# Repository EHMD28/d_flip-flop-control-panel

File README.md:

# D-Type Flip-Flop Control Panel

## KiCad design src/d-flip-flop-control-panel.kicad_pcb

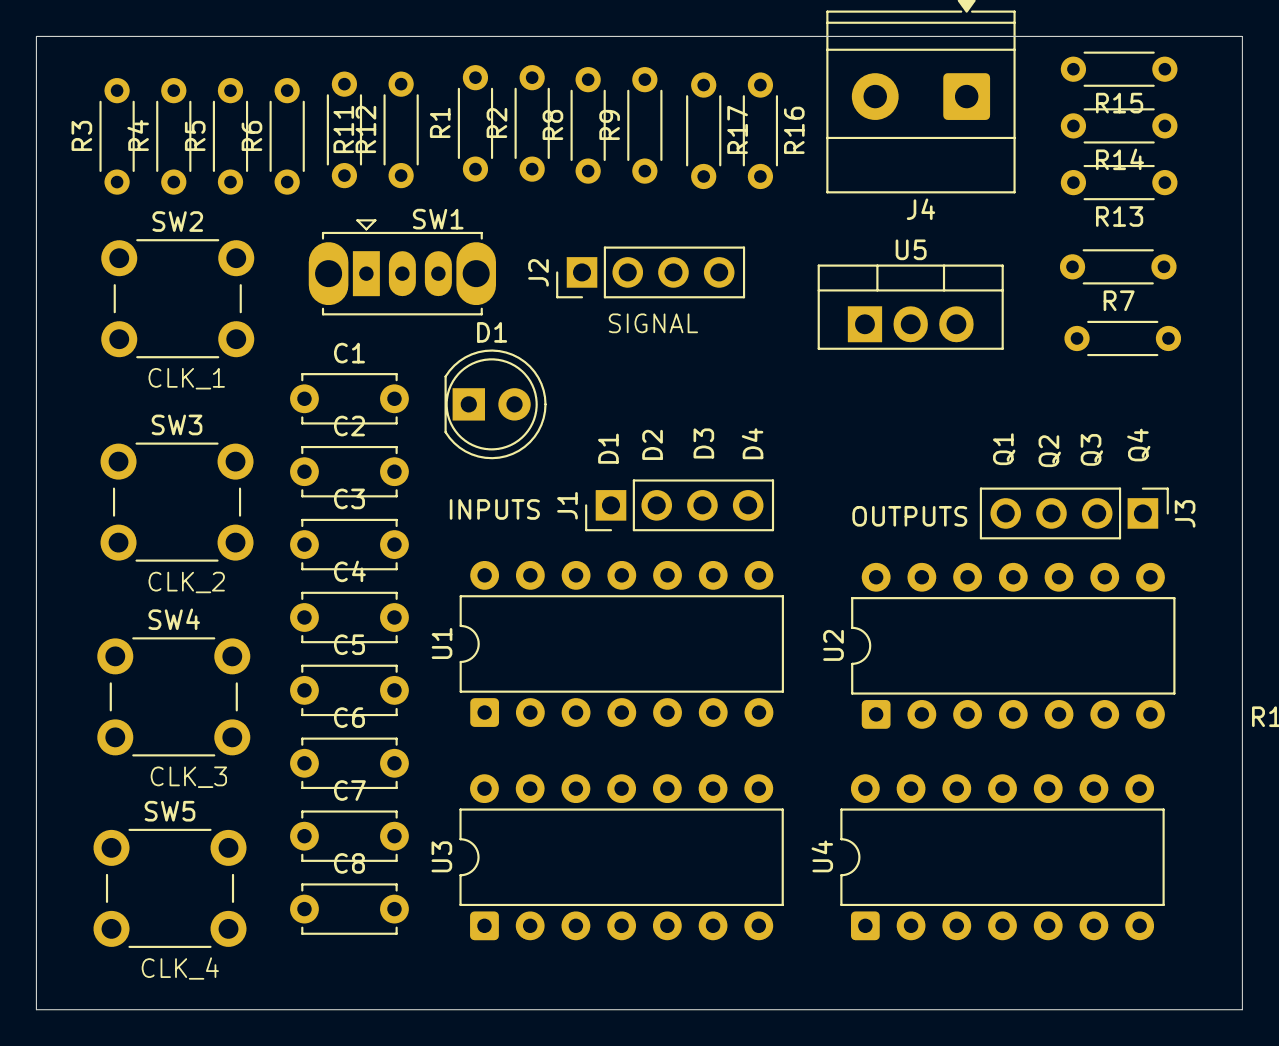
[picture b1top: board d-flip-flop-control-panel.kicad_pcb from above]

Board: 2 copper layers, 67.0 x 54.1 mm, 40 parts (0 on the bottom side), 33 nets, no tracks yet.

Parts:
C1, C2, C3, C4, C5, C6, C7, C8: 100 nF; C_Disc_D5.0mm_W2.5mm_P5.00mm
D1: RED; LED_D5.0mm
J1, J2, J3: Conn_01x04; PinHeader_1x04_P2.54mm_Vertical
J4: Screw_Terminal_01x02; TerminalBlock_Phoenix_MKDS-1,5-2-5.08_1x02_P5.08mm_Horizont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
R1, R2, R3, R4, R6, R7, R8, R9: 10k; R_Axial_DIN0204_L3.6mm_D1.6mm_P5.08mm_Horizontal
R5, R10, R13, R15, R17: 1k; R_Axial_DIN0204_L3.6mm_D1.6mm_P5.08mm_Horizontal
R11, R12, R14, R16: 5k; R_Axial_DIN0204_L3.6mm_D1.6mm_P5.08mm_Horizontal
SW1: SW_SPDT; SW_Slide_SPDT_Straight_CK_OS102011MS2Q
SW2: CLK_1; SW_PUSH_6mm
SW3: CLK_2; SW_PUSH_6mm
SW4: CLK_3; SW_PUSH_6mm
SW5: CLK_4; SW_PUSH_6mm
U1, U2: 74HC74; DIP-14_W7.62mm
U3, U4: 74HC14; DIP-14_W7.62mm
U5: L7805; TO-220-3_Vertical

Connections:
+5V: R4.2, R6.2, R7.2, R9.2, R11.2, R12.2, R14.2, R16.2, SW1.1 (A), U1.4 (~S), U1.10 (~S), U1.14 (VCC), U2.4 (~S), U2.10 (~S), U2.14 (VCC), U3.14 (VCC), U4.14 (VCC), U5.3 (OUT)
/DATA_1: J1.1, R1.2, U1.2 (D)
/DATA_2: J1.2, R2.2, U1.12 (D)
/DATA_3: J1.3, R3.2, U2.2 (D)
/DATA_4: J1.4, R8.2, U2.12 (D)
/OUT_1: J3.4, U1.5 (Q)
/OUT_2: J3.3, U1.9 (Q)
/OUT_3: J3.2, U2.5 (Q)
/OUT_4: J3.1, U2.9 (Q)
GND: C1.2, C2.2, C3.2, C4.2, C5.2, C6.2, C7.2, C8.2, D1.1 (K), J4.2, R1.1, R2.1, R3.1, R8.1, SW1.3 (C), SW2.1, SW3.1, SW4.1, SW5.1, U1.7 (GND), U2.7 (GND), U3.7 (GND), U4.7 (GND), U5.2 (GND)
unnamed: C1.1, R10.2, U3.3
unnamed: C2.1, R6.1, U3.1
unnamed: C3.1, R13.2, U3.5
unnamed: C4.1, R7.1, U3.9
unnamed: C5.1, R15.2, U3.13
unnamed: C6.1, R4.1, U3.11
unnamed: C7.1, R17.2, U4.1
unnamed: C8.1, R9.1, U4.3
unnamed: D1.2 (A), R5.2
unnamed: J2.1, J2.2, J2.3, J2.4, R5.1, SW1.2 (B)
unnamed: R10.1, R11.1, SW2.2
unnamed: R12.1, R13.1, SW3.2
unnamed: R14.1, R15.1, SW4.2
unnamed: R16.1, R17.1, SW5.2
unnamed: U1.3 (C), U3.4
unnamed: U1.1 (~R), U3.2
unnamed: U1.11 (C), U3.6
unnamed: U1.13 (~R), U3.8
unnamed: U2.3 (C), U3.12
unnamed: U2.1 (~R), U3.10
unnamed: U2.11 (C), U4.2
unnamed: U2.13 (~R), U4.4
VCC: J4.1, U5.1 (IN)
